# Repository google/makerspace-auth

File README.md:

# Summary

We started this project with two goals in mind, for Google makerspaces where
employees all have the same kind of RFID badge:

1. Only people authorized (trained) should be able to use dangerous tools
2. We'd like to have reliable access logs for even non-dangerous tools

## Organization

    docs/
      Documentation on the project to include contributions on tool connectivity.
    software/
      The Python client that runs on a Pi.
    hardware/
      The custom Pi hat we use to interact with buttons and a power switch tail.

## Contributing

We *welcome* contributions, especially ones that make this more useful to other
makerspaces.  We'd like this to be a generic solution wherever possible.

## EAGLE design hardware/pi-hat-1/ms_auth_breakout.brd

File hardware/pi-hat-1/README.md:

# Pi Hat 1

This is an example board that fits a Raspberry Pi.  We tried to make it fun
enough to assemble as a beginning soldering exercise (yes, even with surface
mount!), and not use anything too strange.

## Part notes

The odd board shape is to preserve easy access to CSI bus in case you're using
a camera.

We tested with 2x20 headers both cheap (eBay) and expensive
(SFH11-PBPC-D20-ST-BK at $1.97).  All fit, barely clearing the holes.

The top hole is intended as mechanical joining, but as in all Pi hats, needs an
odd size standoff (M2.5 x 11mm).

You don't need both the 2-pin and barrel supply (in fact, don't power both
simultaneously), but having the second set of pads makes probing easier.

The resistor network can be bussed or independent, either will work.  10k
appears sufficient to overpower the onboard pulldown on boot, but 4.7k (less
common) works too.

## Pinouts

The button pinout is (left-to-right with the tab facing down) is (``IN, n/c,
GND, +12V, Switched GND``).  It's intended for a light and/or button per
connector.  Arcade buttons work fairly well if your enclosure is big enough.

The only connector with a freewheeling diode is the 3-pin one marked high current.  It's intended for relay or solenoid use, like for a door.  It's fairly easy to blow the driver chip on all the others.

You can crimp or solder the switch and light side; you should crimp the Molex KK side.

## The 30-second guide to crimping Molex KK

The best tool is Molex 63811-8200, but it's very expensive (350 USD).  We used a budget crimper SN-2549 (23 USD) for these photos, which is the cheapest we've tried that does OK.

For a walkthrough of this process, University of Manchester has produced a video which details the workflow:  [https://www.youtube.com/watch?v=8jcfD1UW8SE](https://www.youtube.com/watch?v=8jcfD1UW8SE)

1. Strip 3mm of wire.

2. Insert into crimper with the open end facing you.

3. Don't crush the spring, which is on the back side, while you close a couple of clicks.  Now insert wire from the front and complete the cycle.

4. This is acceptably crimped.  It's not ideal, but acceptable.

5. Insert into housing with tiny tooth up, and the spring down in this orientation.  It should lock.

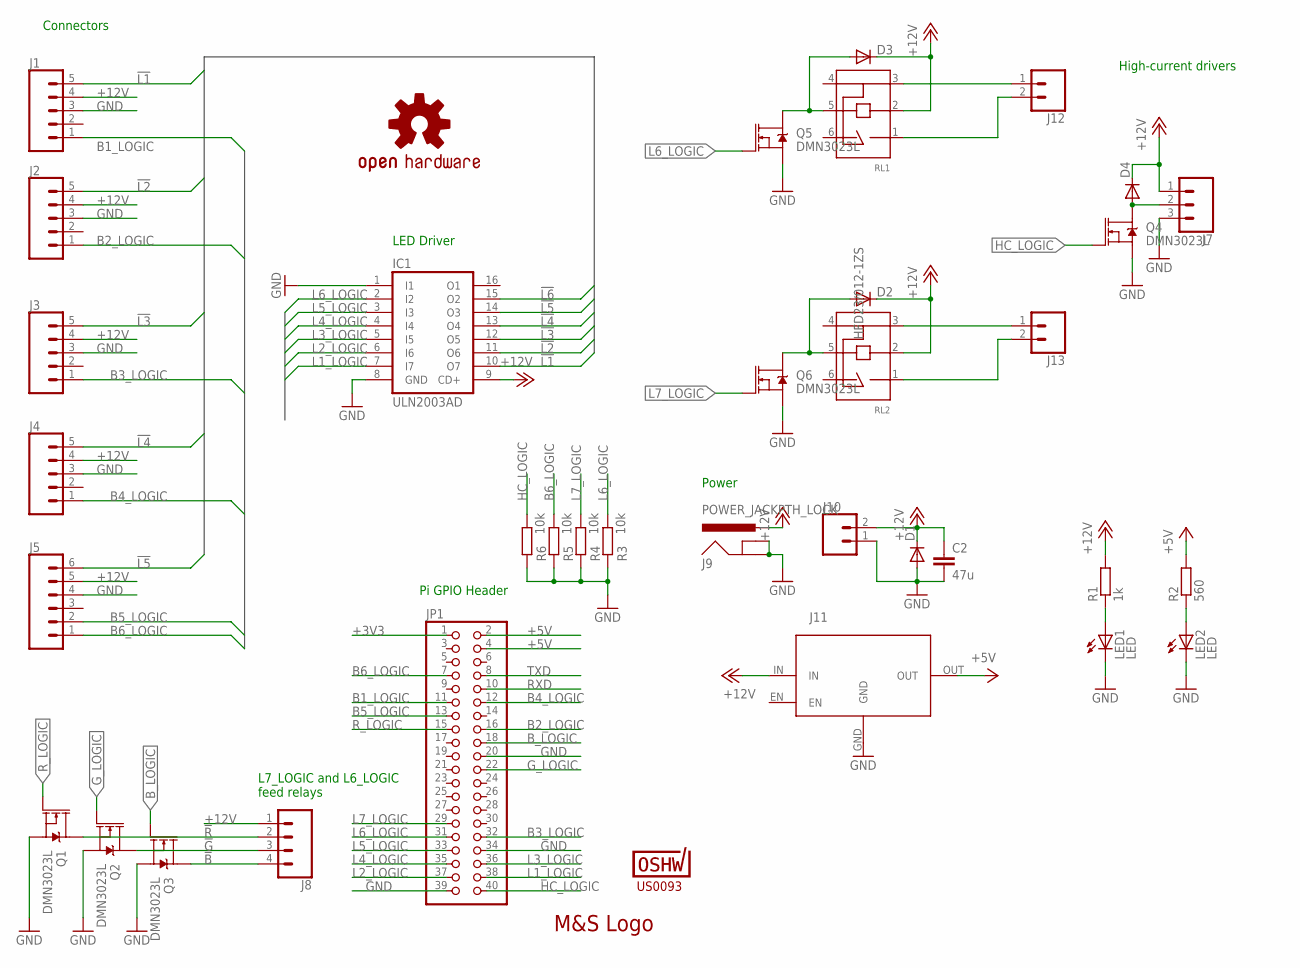
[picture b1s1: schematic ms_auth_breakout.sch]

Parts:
C2: 47u; C1206
D1, D2, D3, D4: DIODE-DO-214AC; DO-214AC
IC1: ULN2003AD; SO16
J1, J2, J3, J4: CONN_05POLAR_LOCK; MOLEX-1X5_LOCK
J5: CONN_06POLAR_LOCK; MOLEX-1X6_LOCK
J7: CONN_03POLAR_LOCK; MOLEX-1X3_LOCK
J8: CONN_04POLAR_LOCK; MOLEX-1X4_LOCK
J9: POWER_JACKPTH_LOCK; POWER_JACK_PTH_LOCK
J10, J12, J13: CONN_02POLAR_LOCK; MOLEX-1X2_LOCK
J11: BUCK_MODULEHORIZONTAL; BUCK_HORIZONTAL
JP1: PINHD-2X20; 2X20
LED1, LED2: LED; CHIPLED_0805
LOGO1: OSHW-LOGOM; OSHW-LOGO-M
Q1, Q2, Q3, Q4, Q5, Q6: DMN3023L; SOT23-3
R1: 1k; R0805
R2: 560; R0805
R3, R4, R5, R6: 10k; R0805
RL1, RL2: HFD23_SPDT; HFD23; MPN HFD23/012-1ZS
U$1: MS_LOGO; MS_LOGO_VECTOR
U$2: US0093; CERT-SMALL-SILK

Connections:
!B: J8.4, Q3.3 (D)
!G: J8.3, Q2.3 (D)
!L1: IC1.10 (O7), J1.5
!L2: IC1.11 (O6), J2.5
!L3: IC1.12 (O5), J3.5
!L4: IC1.13 (O4), J4.5
!L5: IC1.14 (O3), J5.6
!L6: IC1.15 (O2)
!R: J8.2, Q1.3 (D)
+5V: J11.OUT, JP1.2, JP1.4, R2.2; also elsewhere on the board
+12V: C2.1, D1.C, D2.C, D3.C, D4.C, IC1.9 (CD+), J1.4, J2.4, J3.4, J4.4, J5.5, J7.1, J8.1, J9.PWR, J10.2, J11.IN, R1.2, RL1.2, RL2.2
B1_LOGIC: J1.1, JP1.11; also elsewhere on the board
B2_LOGIC: J2.1, JP1.16; also elsewhere on the board
B3_LOGIC: J3.1, JP1.32; also elsewhere on the board
B4_LOGIC: J4.1, JP1.12; also elsewhere on the board
B5_LOGIC: J5.2, JP1.13; also elsewhere on the board
B6_LOGIC: J5.1, JP1.7, R5.2; also elsewhere on the board
B_LOGIC: JP1.18, Q3.1 (G); also elsewhere on the board
GND: C2.2, D1.A, IC1.1 (I1), IC1.8 (GND), J1.3, J2.3, J3.3, J4.3, J5.4, J7.3, J9.GND, J9.GNDBREAK, J10.1, J11.GND, JP1.20, JP1.34, JP1.39, LED1.C, LED2.C, Q1.2 (S), Q2.2 (S), Q3.2 (S), Q4.2 (S), Q5.2 (S), Q6.2 (S), R3.1, R4.1, R5.1, R6.1; also elsewhere on the board
G_LOGIC: JP1.22, Q2.1 (G); also elsewhere on the board
HC_LOGIC: JP1.40, Q4.1 (G), R6.2; also elsewhere on the board
L1_LOGIC: IC1.7 (I7), JP1.38; also elsewhere on the board
L2_LOGIC: IC1.6 (I6), JP1.37; also elsewhere on the board
L3_LOGIC: IC1.5 (I5), JP1.36; also elsewhere on the board
L4_LOGIC: IC1.4 (I4), JP1.35; also elsewhere on the board
L5_LOGIC: IC1.3 (I3), JP1.33; also elsewhere on the board
L6_LOGIC: IC1.2 (I2), JP1.31, Q5.1 (G), R3.2; also elsewhere on the board
L7_LOGIC: JP1.29, Q6.1 (G), R4.2; also elsewhere on the board
unnamed: D2.A, Q6.3 (D), RL2.5
unnamed: D4.A, J7.2, Q4.3 (D)
unnamed: D3.A, Q5.3 (D), RL1.5
unnamed: J12.2, RL1.1
unnamed: LED2.A, R2.1
unnamed: J13.2, RL2.1
unnamed: J12.1, RL1.3
unnamed: LED1.A, R1.1
unnamed: J13.1, RL2.3
R_LOGIC: JP1.15, Q1.1 (G); also elsewhere on the board

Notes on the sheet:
Pi GPIO Header
LED Driver
Connectors
Power
High-current drivers
L7_LOGIC and L6_LOGIC feed relays

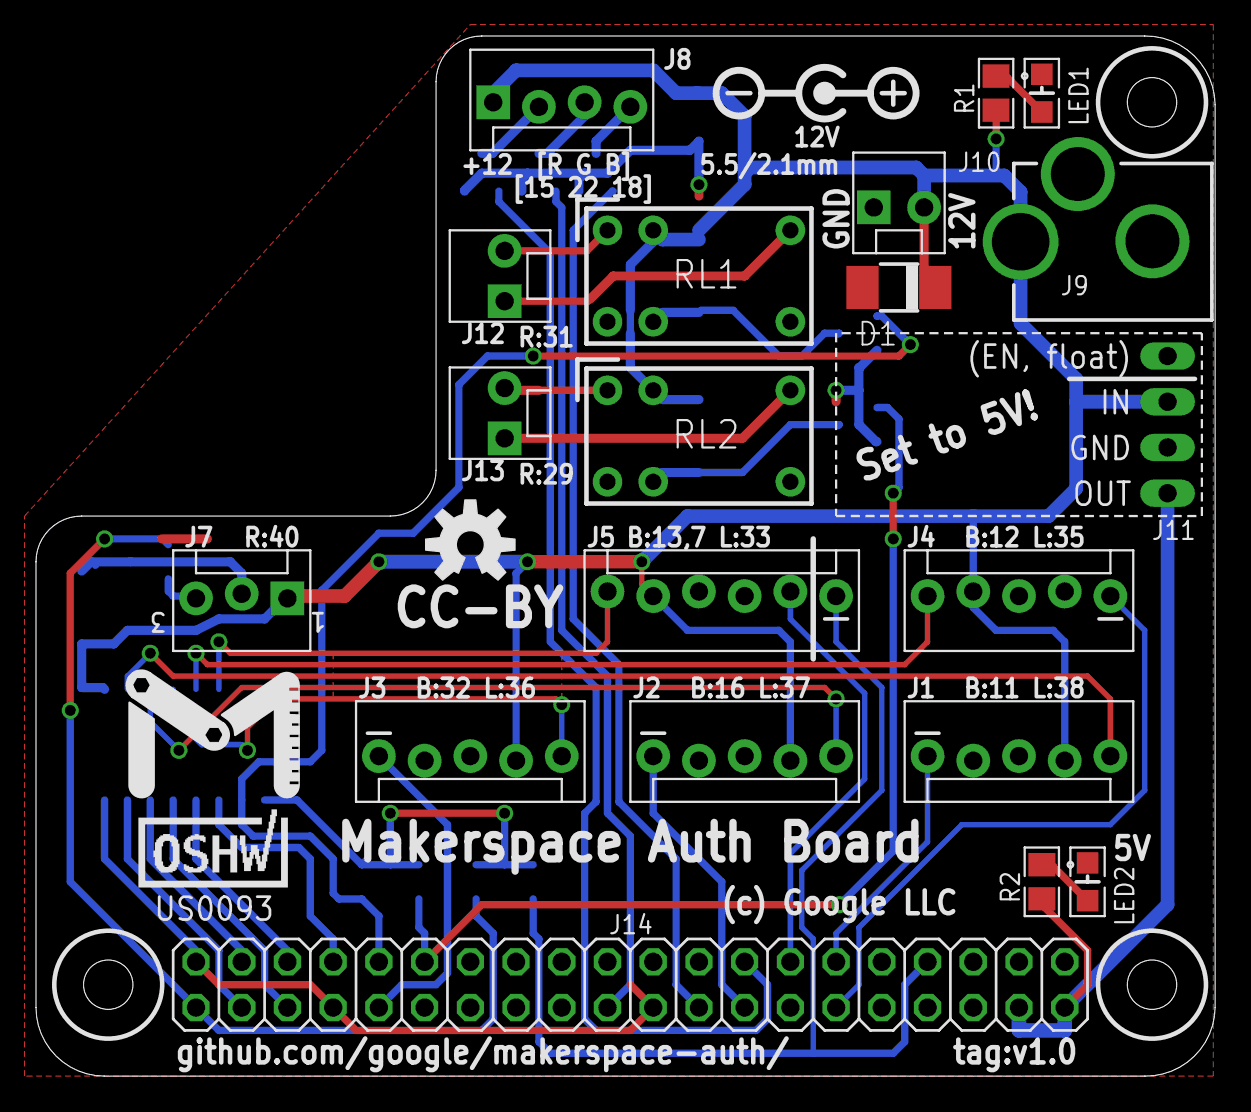
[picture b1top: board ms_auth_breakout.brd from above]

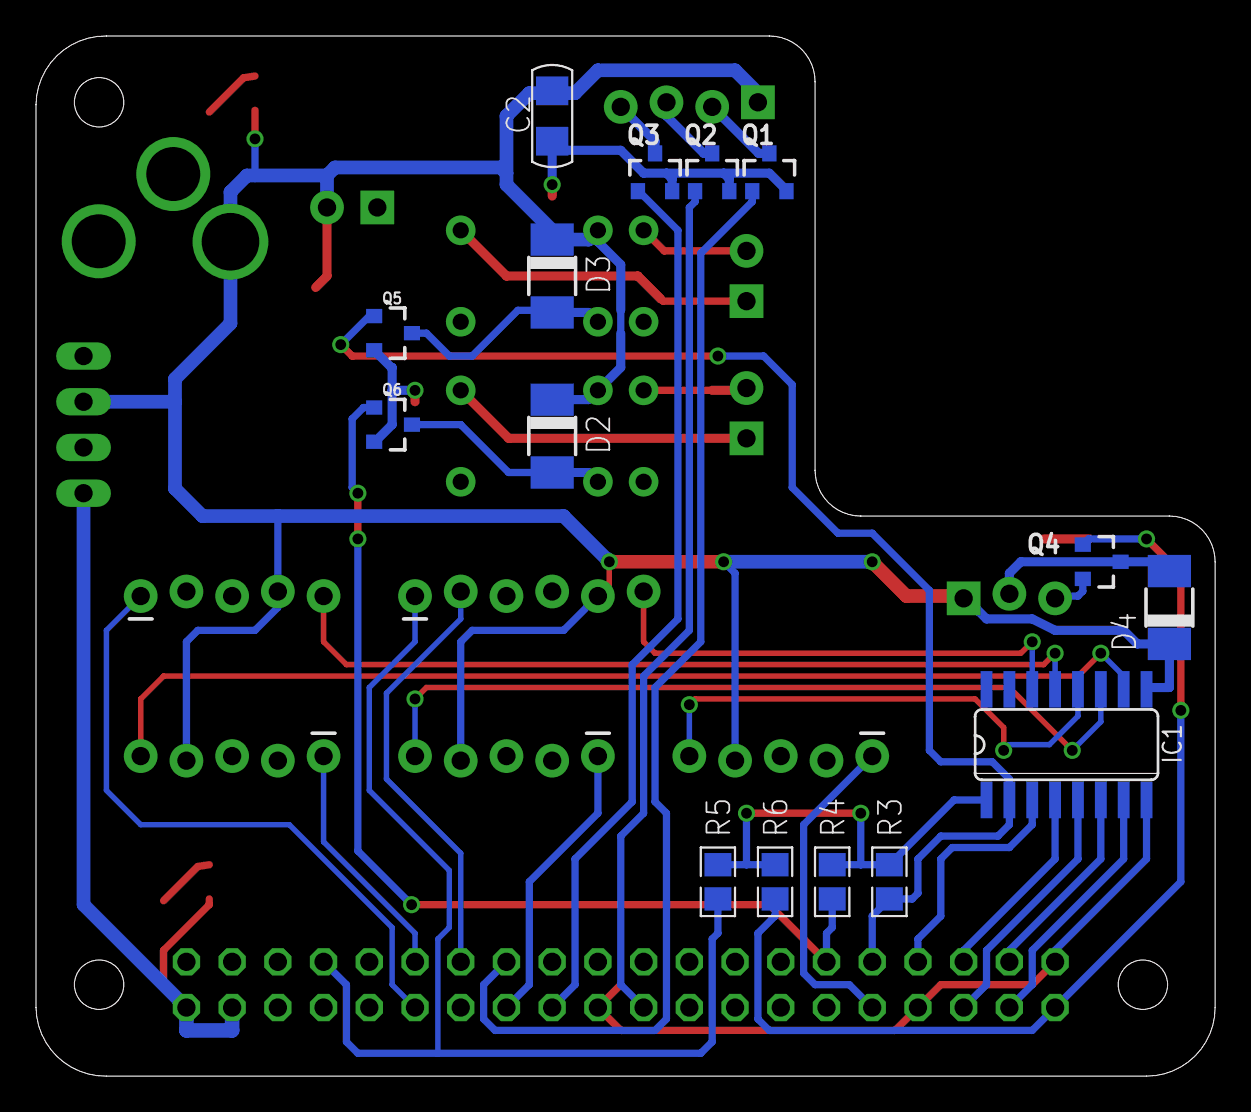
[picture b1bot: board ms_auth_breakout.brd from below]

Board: 2 copper layers, 65.5 x 57.8 mm, 38 parts (15 on the bottom side), 37 nets.

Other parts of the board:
J14: 2X20

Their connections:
+5V: J14.2, J14.4; also elsewhere on the board
B1_LOGIC: J14.11; also elsewhere on the board
B2_LOGIC: J14.16; also elsewhere on the board
B3_LOGIC: J14.32; also elsewhere on the board
B4_LOGIC: J14.12; also elsewhere on the board
B5_LOGIC: J14.13; also elsewhere on the board
B6_LOGIC: J14.7; also elsewhere on the board
B_LOGIC: J14.18; also elsewhere on the board
GND: J14.20, J14.34, J14.39; also elsewhere on the board
G_LOGIC: J14.22; also elsewhere on the board
HC_LOGIC: J14.40; also elsewhere on the board
L1_LOGIC: J14.38; also elsewhere on the board
L2_LOGIC: J14.37; also elsewhere on the board
L3_LOGIC: J14.36; also elsewhere on the board
L4_LOGIC: J14.35; also elsewhere on the board
L5_LOGIC: J14.33; also elsewhere on the board
L6_LOGIC: J14.31; also elsewhere on the board
L7_LOGIC: J14.29; also elsewhere on the board
R_LOGIC: J14.15; also elsewhere on the board

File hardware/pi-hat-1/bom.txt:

Main

    Qty P/N             Ref     Description
    1   22-23-2021      J10     2p Molex KK
    1   22-23-2031      J       3p Molex KK
    1   22-23-2041      J8      4p Molex KK
    6   22-23-2051      J1-6    5p Molex KK
    1   S9200-ND        JP1     2x20p female header
    1   4609X-101-103LF RN1     SIL resistor
    1   C3216JB1E476M160AC  C2  47u 1206 cap
    1   694106301002    J9      Barrel Jack
    1   ULN2003ADR      IC1     ULN2003AD
    2   LG R971-KN-1    LED1,LED2  LED
    2   SS14CT-ND       D1      SMA diode 1A
    4   DMN3023L-7      Q1-Q4   N-ch FET
    1   1k 0603         R1
    1   470R 0603       R2

Mating Parts

    08-50-0114
    22-01-3027
    22-01-3037
    22-01-3047
    22-01-3057

w/ 3p buck add

    1   OKI-78SR-5/1.5-W36H-C       J11

w/ 4p buck add

    1   "24v mini adjustable buck converter 3a" from ebay       J11
    1   4p header                                               (for J11)

If using relay outputs, you may omit J5,J6, and add:

    2   DMN3023L-7      Q5,Q6   N-ch FET
    2   22-23-2021      J12,J13 2p Molex KK
    one-of {
      2   HFD23 12V       RL1,RL2
      2   SS14CT-ND       D2,D3
    or
      2   CPC1017         IC3,IC4
      2   1k 0805         R3,R4
    }

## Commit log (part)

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2017-01-24 Add first board, update readmes and gitignore
2017-01-25 Version 0.1 of Auth software.
2017-01-26 Added license blocks & cleaned up formatting for v0.1
2017-01-26 Cleaned formatting for v0.1
2017-02-02 Added newlines to findKeyboards.py and main.py
2017-02-02 Added newline to main.py
2017-02-03 Improved twoButtonExample.py's main
    Removed an unnecessary if statement in twoButtonExample.
    Added newlines to auth_lib and twoButtonExample.
2017-02-08 Board v0.2 sent to fab.
    This now has 5 button headers, a dedicated PowerSwitch Tail header, and
    a dedicated buzzer. Buck converter has been moved onboard, and we
    connect to a 3rd mounting hole for stability. Since there's room, add a
    barrel jack.
    This version includes the pin number on silkscreen next to each item.
    The 5-pin locking part isn't yet upstreamed to SparkFun's library.
2017-02-08 Begin v0.3 of auth board
    Improve 12V trace routing down the middle; swap to vector logo.
2017-03-10 Getting ready to order pi-hat-1 v0.3
    I re-routed this almost completely. The area in the middle now makes a bit
    more sense, and there's only one ground island that had to be reconnected.
    * Switched back to buck module
    * Found room for 6 button connectors again
    * Added discrete RGB LED driver
    * Added higher current output for inductive loads
2017-03-10 Reroute +12 line to avoid ground island
2017-03-10 Update pi-hat-1 board image
2017-04-04 Add client API and two-button example.
2017-04-04 Improve class hierarchy and naming for GPIO
2017-04-20 Add snapshot of the bracket I use.
2017-04-29 Ensure everything works reasonably on Pi 3 hardware.
    This is a much more complete example that involves buzzer and various
    shell scripts for local logging.
2017-04-29 Add missing licenses
2017-05-01 Address some of Uriah's verbal comments
2017-05-02 Update software readme
2017-05-02 Add crimping docs
2017-05-28 Add libs for relay and opto
2017-05-28 Rework board to add two relays.
    Also remove buzzer, change LED connector, and standardize on smaller
    freewheel diodes. Not quire ready for 0.4 cut; needs airwires routed
    for relays with solder jumpers.
2017-05-28 Fix buck-module ENABLE pin location
2017-06-07 pi-hat-1 v0.4 as-ordered
    (Forgot to route the relay connections though.)
2017-06-13 Forgot to note J12/13 optional.
2017-06-28 Support multiple sinks
2018-01-11 Add sound support, minor tweaks
2018-01-17 Authboard change for v1.0
    - Remove SOP-4 optos (most test boards we assembled with relays)
    - Remove J6 (most test boards for laser need 3 outputs)
    - Swap SIP resistor for 4x discrete (easier to mass-produce without it)
    - Improve silkscreen around polarity and buck module
    - Add MPN/MFN to parts on board. (Should this go in schematic?)
    - Change J5 to support a 3-position switch, intended for marking
2018-01-18 Add relay MPN, OSH Certification mark
2018-01-18 Increase size of buckmodule drill
2018-02-06 Switch diode part number, add resistors, minor trace tweak
2018-02-28 Update for 2018. Minor behavior changes.
    - button callback now includes self instead of config_name
    - Main loop prints traceback on exceptions
    - Single beep now available on buzzer
2018-02-28 Add QA script to exercise all buttons/lights/relays
2018-02-28 Split out tonal buzzer (non-working)
2018-02-28 Add enable for speaker-sounds, fix pins
2018-03-06 Fix stack trace in gpio_buzzer.py:39
    Add 1-length tuple instead of bare integer to set_queue in on() and off() methods because that's what run_inner() expectes. Fixes the following error:
    File "/home/pi/makerspace-auth/software/authbox/api.py", line 122, in run
    self.run_inner()
    File "/home/pi/makerspace-auth/software/authbox/gpio_buzzer.py", line 39, in run_inner
    next_mode = item[0]
2018-03-06 Fix stack trace in gpio_buzzer.py:39
    Add 1-length tuple instead of bare integer to set_queue in on() and off()
    methods because that's what run_inner() expectes. Fixes the following error:
    File "/home/pi/makerspace-auth/software/authbox/api.py", line 122, in run
    self.run_inner()
    File "/home/pi/makerspace-auth/software/authbox/gpio_buzzer.py", line 39,
    in run_inner
2018-03-08 Call GPI.cleanup() on exit to turn off lights and relays.
2018-03-08 Add Button.blink(count=0) to blink a finite number of times.
    Can be used for visual confirmation of an action or for blinking out an
    error code when something goes wrong.
2018-03-08 Blink red light if badge rejected or green button pushed when not authed
    Provides visual confirmation in addition to hearing the beep. Useful in
    noisy environments or if the buzzer is not installed.
2018-03-08 Explicitly set GPIO outputs to initial state on startup.
    Code expects most GPIOs will output low when enabled on startup.
    This is the case after a hard reset, but it's possible GPIOs outputs
    were manually enabled and set high before software start. Setting
    them on startup ensures the pin state matches what the software
    expects. Most GPIOs are initialized low. ActiveLow Relay will be
    initialized high.
2018-05-16 Reformat docs
2018-05-16 Ignore backups
2018-05-16 Round slots for easier cnc routing
2018-05-16 Regen plates
2018-05-16 Update shelf to not require support
    This improves the hard support that didn't play nice with Cura's
    "concentric" solid layers, since it apparently doesn't do bridging.
2018-05-16 Begin docs
2018-05-16 Add plate with both for better lasercutting
2018-05-16 Add templates for sides and lid
2018-05-16 Improve docs.
2018-05-16 Add Epilog docs
2018-05-16 Add letters for easier plate alignment
2018-05-16 Make one box mount slightly shorter, regen.
    This lets us cut the inner+outer on the same stock on a Mini 24.
2018-05-16 Synchronize docs.
2018-05-18 doc: Add video link for Molex crimping
    Molex crimping isn't hard per se, but walking through the process makes
    everything a bit more clear. While the photos in the repo were a
    wonderful start, this added a bit more context which was very helpful.
2018-05-18 doc/bug: Fixing 404 errors in docs
    Recent changes to the docs were using incorrect filenames in the
    documentation (missing the `.md` file extention which is required for
    files beyond `README.md` as the default in a directory).
    doc: Updating main README.md, removing stale data
    Previously the main README.md in the project referenced a sample python
    server which is no longer a part of the project. Additionally, there is
2018-05-21 Add tests and improve docs for client code.
2018-05-21 Add test of the basic logic in two_button.py
2018-05-21 Improve compare_log to depend on order and count.
2018-05-22 Ensure tests can run on a Pi by using fake-rpi
2018-05-22 Rename sound support config names
2018-05-22 Add defaults to config
2018-05-22 Add traffic light support.
    Also update default command lines to include explicit positional parameters.
2018-05-24 Config support for default suffix, simple floats
2018-05-24 two_button.py now takes a filename, not a path.
    This allows for overriding with an arbitrary number of configs,
    especially ones that aren't checked in.
2018-05-24 Uncomment base_args so overriding commands can enable http api
2018-05-24 Remove support for playing sounds
    Since there is an obvious place for making sounds, this is less
    important to include out of the box. Buzzers seem more effective at
    notifying users, so we keep that.
2018-06-29 fix typo in barrel jack part number
2018-07-09 Support simple backslash escapes in config
2018-10-30 Avoid commit issues with sample credential files
    The file `sample_auth_check.sh` refers to two files which should not be
    kept in revision control:
    - `authorized.txt`
    - `logs.txt`
    This addition to `.gitignore` keeps those files from accidentally being
    commited.
2019-05-29 device: Wiegand badge reader support
    This commit provides support for [Wiegand][1] style badge readers. It has
    been tested with a number of EM4100 style readers and has been used in
    production for a number of months without issue.
    The wiring for a badge reader requires two data GPIO pins as input.
    These pins within the Wiegand protocol are "D0" and "D1" respectively.
    Normally, these pins are pulled high (generally to 5v). They perform
2019-06-30 Add tests and switch to queue for badgereader_wiegand.
    The queue actually makes the testing logic way easier.
2019-06-30 FIX: Making requested changes to #28
    In pr/#28 @thatch requested a number of changes made. Some of which
    were handled in the previous cherry pick the rest of which are added in
    this commit.
2019-07-01 Initial python 3 porting done. Tests pass.
2019-09-20 contrib: Systemd Unit
    Setup of a contrib directory and a corresponding systemd unit to handle
    startup of makerspace auth on the Raspberry Pi.
2019-11-14 Fix broken test_badgereader_wiegand_gpio.py unit test
2019-11-14 Eliminate mostly-busy wait in badgereader_wiegand_gpio.py
2019-11-18 Add setuptools metadata
2019-11-18 Speed up tests drastically, cover timer
2019-11-18 Format with isort+black
2019-11-18 Fix tests on 2.7
2019-11-18 Get lint clean
2019-11-18 Enable github actions for continuous testing
2019-11-20 Adding checks for the VirtualEnv as well as packages required on raspbian.
2019-11-21 Fix docstring indentation after Python Black reformat
    Black changed the indent from 2 to 4 spaces but it doesn't seem
    to handle docstring indentation at all.
2019-11-21 Blink red light once if badge rejected or green button pushed when not authed
    Provides visual confirmation in addition to hearing the beep. Useful in
    noisy environments or if the buzzer is not installed.
2019-11-22 Metadata changes
    - build universal (py2/py3) wheel
    - move coverage args to setup.cfg
    - add python_requires
2019-11-22 Include LICENSE symlink
2019-12-11 Adding lockbox variant
2020-10-13 Replace Eagle design files with KiCad counterparts
2020-10-13 Add PDF with schematic
2020-10-13 Replace existing BOM with the one generated from KiCad
2020-10-30 Add generated gerber files
2020-10-30 Add PDF plots of copper layers and silkscreen markings
2022-06-10 adding repo exemption for allstar security scanner
2023-02-28 Update tox to use new terminology
2023-03-02 Update requirements to newer versions and drop python2 support
2023-03-02 Remove deprecated --recursive flag for lint
2024-03-20 Bump black from 23.1.0 to 24.3.0 in /software
    Bumps [black](https://github.com/psf/black) from 23.1.0 to 24.3.0.
    - [Release notes](https://github.com/psf/black/releases)
    - [Changelog](https://github.com/psf/black/blob/main/CHANGES.md)
    - [Commits](https://github.com/psf/black/compare/23.1.0...24.3.0)
    ---
    updated-dependencies:
2024-04-17 Explicitely enable input pull-ups for button GPIO
2024-04-17 Add beep and blink on press of abort button + immediately turn off the output
2024-04-17 Fix typos
2024-04-18 Only debounce when a callback handler is registered
2024-04-27 Cancel `expire_timer` on abort
    If a user triggers abort using the `off_button`, `expire_timer` is currently still running. In these cases, the authbox will beep after the expiration time even if the authbox is no longer authorized.
    This change fixes this bug by canceling `expire_timer` in `abort`.
2025-01-16 Create readme.md
    Added instructions for using the DLI IoT relay with the makerspace-auth
2025-03-04 Update tests
2025-03-04 Migrate from RPi.GPIO to gpiozero
2026-03-25 Run lint/format across all files
    * Update the makefile to run them against all python files.
    * Fix syntax error in requirements_dev.txt (trailing period).
    * Update flake8 to v5.
    * Fix broken imports in unit tests
    * Run `make format` to get all files into a lint-clean state in preparation for future work.
    * Fix errors called out by `make lint`
2026-03-26 Add AGENTS.md with instructions on how to build and test the software directory
2026-06-16 Update Github Actions to recent Python versions
2026-06-16 Remove Python2 Compatibility

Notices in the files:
hardware/pi-hat-1/ms_auth_breakout.brd:
CC-BY
parts and their libraries:
SparkFun-Connectors: Licensing: Creative Commons ShareAlike 4.0 International - https://creativecommons.org/licenses/by-sa/4.0
